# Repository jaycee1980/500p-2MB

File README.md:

# A500+ 2MB DRAM

Details to come

## License
The hardware is licensed under the [Creative Commons non-commercial license](https://creativecommons.org/licenses/by-nc/4.0/)

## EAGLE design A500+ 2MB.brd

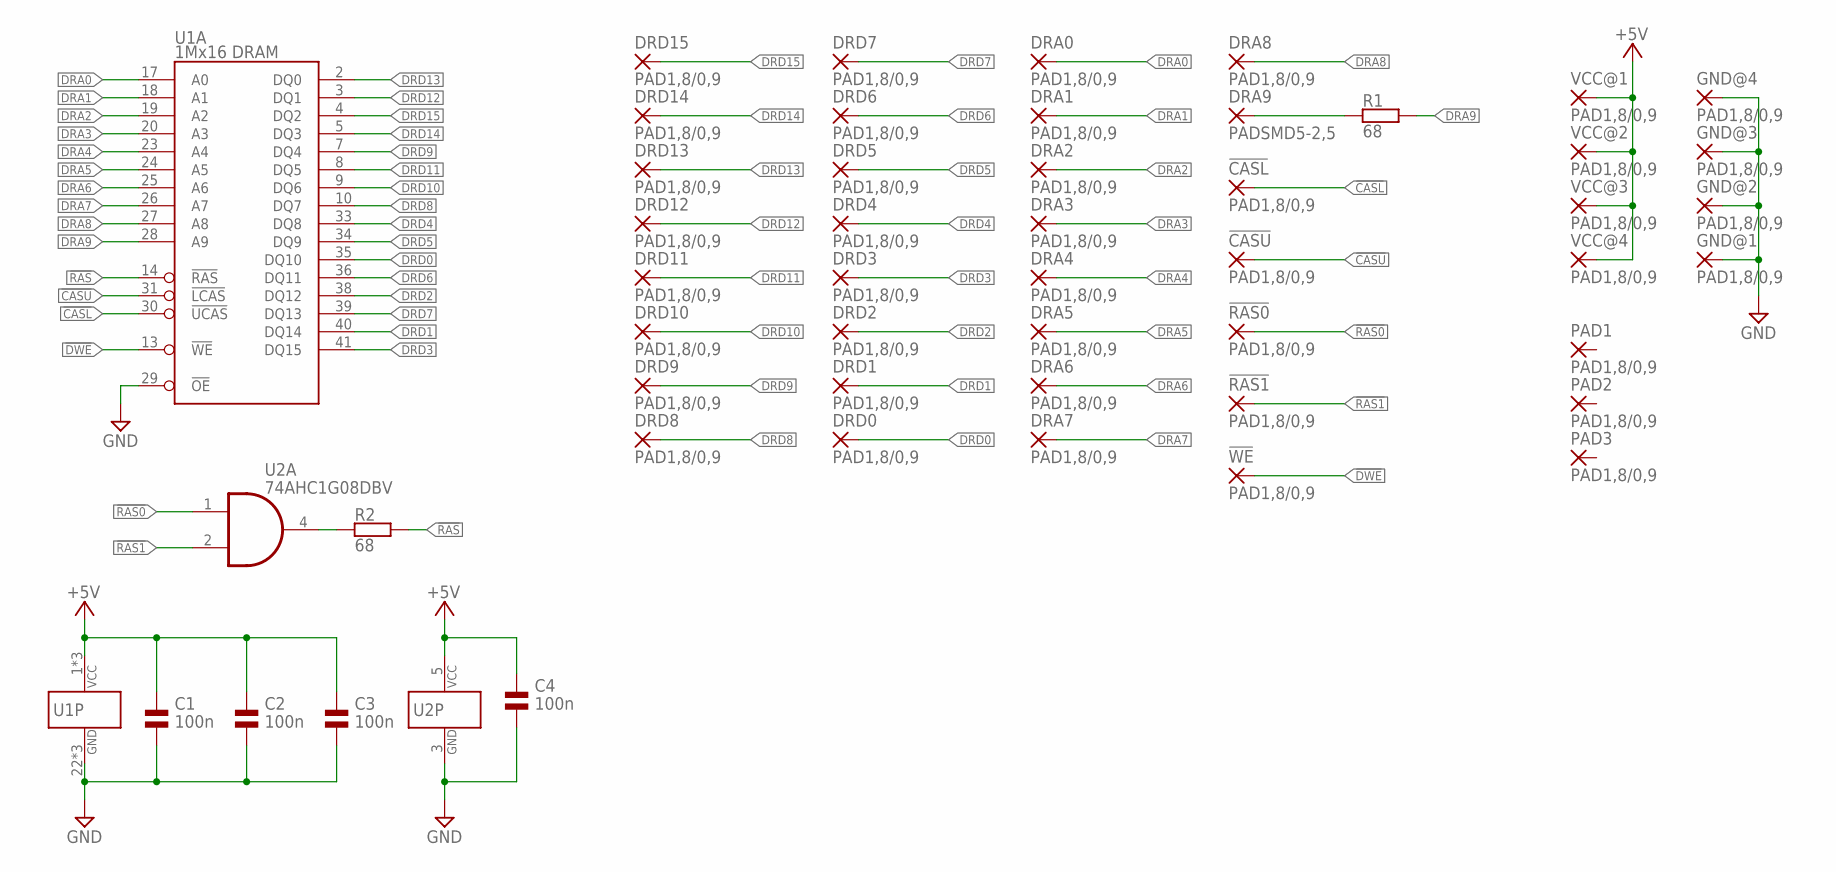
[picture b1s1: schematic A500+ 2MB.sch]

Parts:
!CASL: PAD1,8/0,9; 1,8/0,9
!CASU: PAD1,8/0,9; 1,8/0,9
!RAS0, !RAS1: PAD1,8/0,9; 1,8/0,9
!WE: PAD1,8/0,9; 1,8/0,9
C1, C2, C3, C4: 100n; 0603
DRA0, DRA1, DRA2, DRA3, DRA4, DRA5, DRA6, DRA7, DRA8: PAD1,8/0,9; 1,8/0,9
DRA9: PADSMD5-2,5; 5-2,5
DRD0, DRD1, DRD2, DRD3, DRD4, DRD5, DRD6, DRD7, DRD8, DRD9, DRD10, DRD11, DRD12, DRD13, DRD14, DRD15: PAD1,8/0,9; 1,8/0,9
GND@1, GND@2, GND@3, GND@4: PAD1,8/0,9; 1,8/0,9
PAD1, PAD2, PAD3: PAD1,8/0,9; 1,8/0,9
R1, R2: 68; 0603
U1: 1Mx16 DRAM; SOJ42/4
U2: 74AHC1G08DBV; SOT23-5
VCC@1, VCC@2, VCC@3, VCC@4: PAD1,8/0,9; 1,8/0,9

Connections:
!CASL: !CASL.1, U1.30 (!UCAS)
!CASU: !CASU.1, U1.31 (!LCAS)
!DWE: !WE.1, U1.13 (!WE)
!RAS: R2.2, U1.14 (!RAS)
!RAS0: !RAS0.1, U2.1 (I0)
!RAS1: !RAS1.1, U2.2 (I1)
+5V: C1.1, C2.1, C3.1, C4.1, U1.1 (VCC), U1.6 (VCC), U1.21 (VCC), U2.5 (VCC), VCC@1.1, VCC@2.1, VCC@3.1, VCC@4.1
DRA0: DRA0.1, U1.17 (A0)
DRA1: DRA1.1, U1.18 (A1)
DRA2: DRA2.1, U1.19 (A2)
DRA3: DRA3.1, U1.20 (A3)
DRA4: DRA4.1, U1.23 (A4)
DRA5: DRA5.1, U1.24 (A5)
DRA6: DRA6.1, U1.25 (A6)
DRA7: DRA7.1, U1.26 (A7)
DRA8: DRA8.1, U1.27 (A8)
DRA9: R1.2, U1.28 (A9)
DRA9_: DRA9.1, R1.1
DRD0: DRD0.1, U1.35 (DQ10)
DRD1: DRD1.1, U1.40 (DQ14)
DRD2: DRD2.1, U1.38 (DQ12)
DRD3: DRD3.1, U1.41 (DQ15)
DRD4: DRD4.1, U1.33 (DQ8)
DRD5: DRD5.1, U1.34 (DQ9)
DRD6: DRD6.1, U1.36 (DQ11)
DRD7: DRD7.1, U1.39 (DQ13)
DRD8: DRD8.1, U1.10 (DQ7)
DRD9: DRD9.1, U1.7 (DQ4)
DRD10: DRD10.1, U1.9 (DQ6)
DRD11: DRD11.1, U1.8 (DQ5)
DRD12: DRD12.1, U1.3 (DQ1)
DRD13: DRD13.1, U1.2 (DQ0)
DRD14: DRD14.1, U1.5 (DQ3)
DRD15: DRD15.1, U1.4 (DQ2)
GND: C1.2, C2.2, C3.2, C4.2, GND@1.1, GND@2.1, GND@3.1, GND@4.1, U1.22 (GND), U1.29 (!OE), U1.37 (GND), U1.42 (GND), U2.3 (GND)
unnamed: R2.1, U2.4 (O)

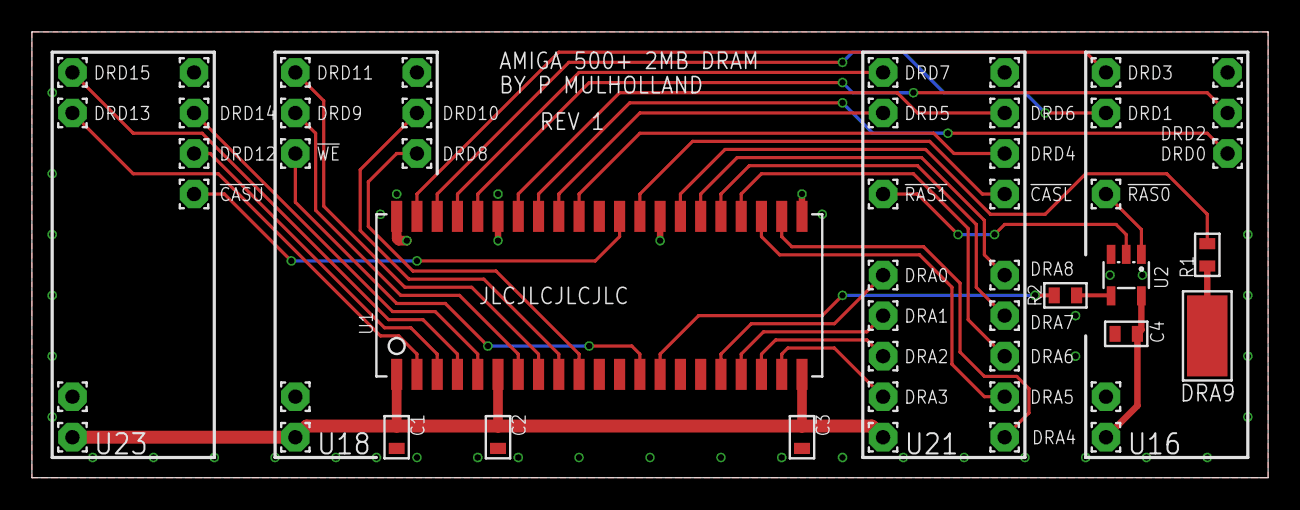
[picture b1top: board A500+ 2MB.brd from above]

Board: 2 copper layers, 77.5 x 27.9 mm, 50 parts (0 on the bottom side), 36 nets.

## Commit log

2025-10-24 Add board image
2025-12-12 Latest version
2025-12-12 Parts list
2025-12-12 Fixed parts list
2025-12-12 added designator column in parts
